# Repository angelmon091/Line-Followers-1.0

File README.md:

# Line Follower 1.0

Robot seguidor de línea — código Arduino, esquemas KiCad y Gerbers listos para fabricación.

Qué es:
- Código, PCB y archivos Gerber para un robot seguidor de línea (ejemplos en `CODE/Main Code/`).

Cómo reproducir (resumen):
1. Materiales: placa Arduino (Uno/Nano/Pro Mini), motores, driver de motores, sensores IR, batería, cables, PCB o protoboard.
2. Abrir el ejemplo: `CODE/Main Code/<ejemplo>/*.ino`.
3. Instalar librerías desde `CODE/Libreria/` y seleccionar la `board` correcta en Arduino IDE/PlatformIO.
4. Compilar y subir al microcontrolador.
5. Montar la electrónica según `ESQUEMA Y PCB/` y/o fabricar la PCB usando `Archivos Gerber PCB/gerbers/` (enviar a fabricante).

Notas importantes:
- Verificar voltaje y polaridad de la batería.
- Calibrar sensores antes de pruebas.
- Revisar conexiones del driver de motores para evitar cortocircuitos.

Estructura del proyecto (estilo `eza --tree`):
```
.
├─ CODE/
│  ├─ Libreria/
│  └─ Main Code/
│     ├─ Codigo Carro V1.0/
│     │  └─ Programacion.ino
│     ├─ Ejemplo de Lectura y Posicion/
│     │  └─ LECTURA_Y_POSICION.ino
│     └─ Ejemplo de Motores y Rotacion/
│        └─ Motores.ino
├─ ESQUEMA Y PCB/
│  ├─ asda.kicad_pcb
│  └─ asda.kicad_sch
├─ Archivos Gerber PCB/
│  └─ gerbers/
│     ├─ asda-F_Cu.gbr
│     └─ asda-job.gbrjob
├─ GErber con Turbina/
└─ README.md
```

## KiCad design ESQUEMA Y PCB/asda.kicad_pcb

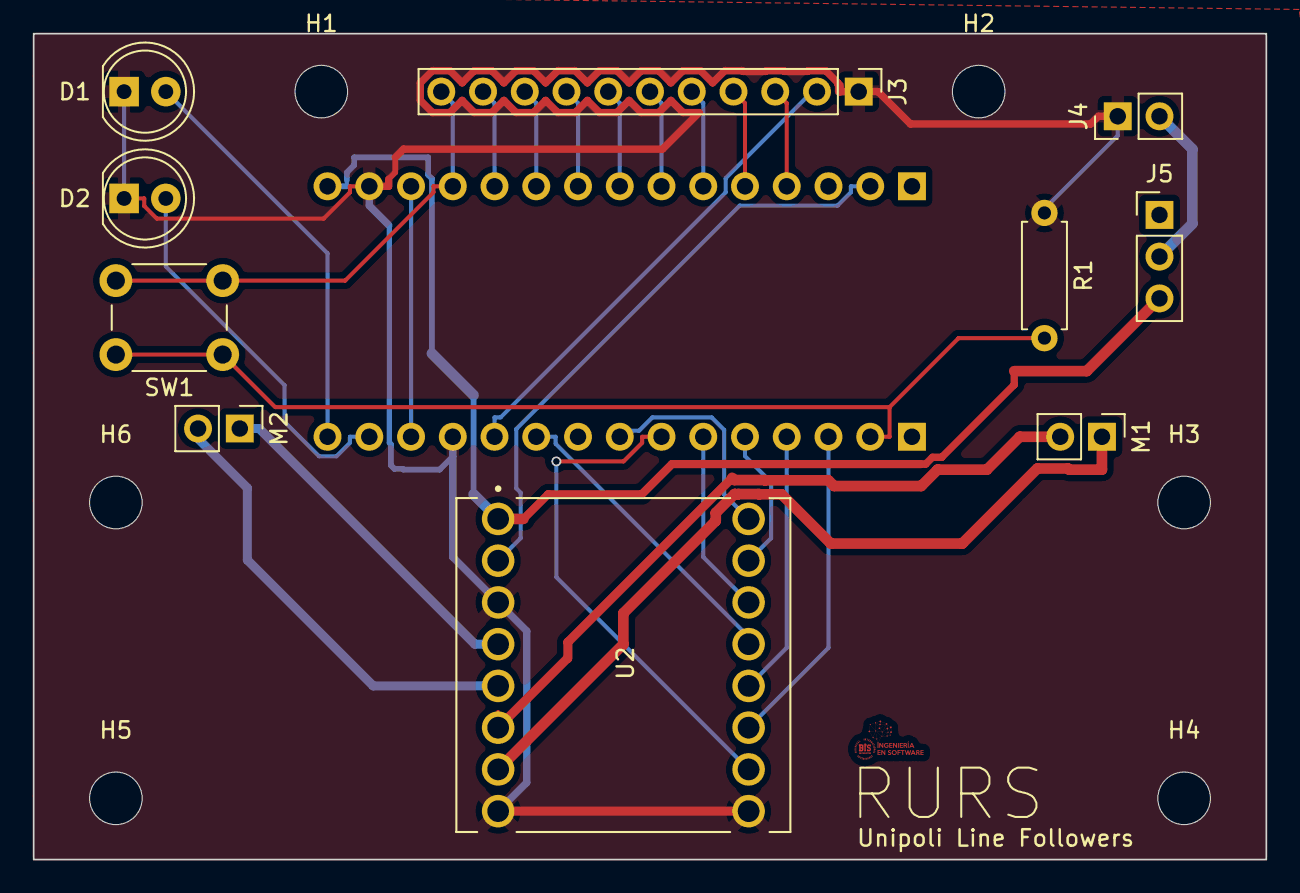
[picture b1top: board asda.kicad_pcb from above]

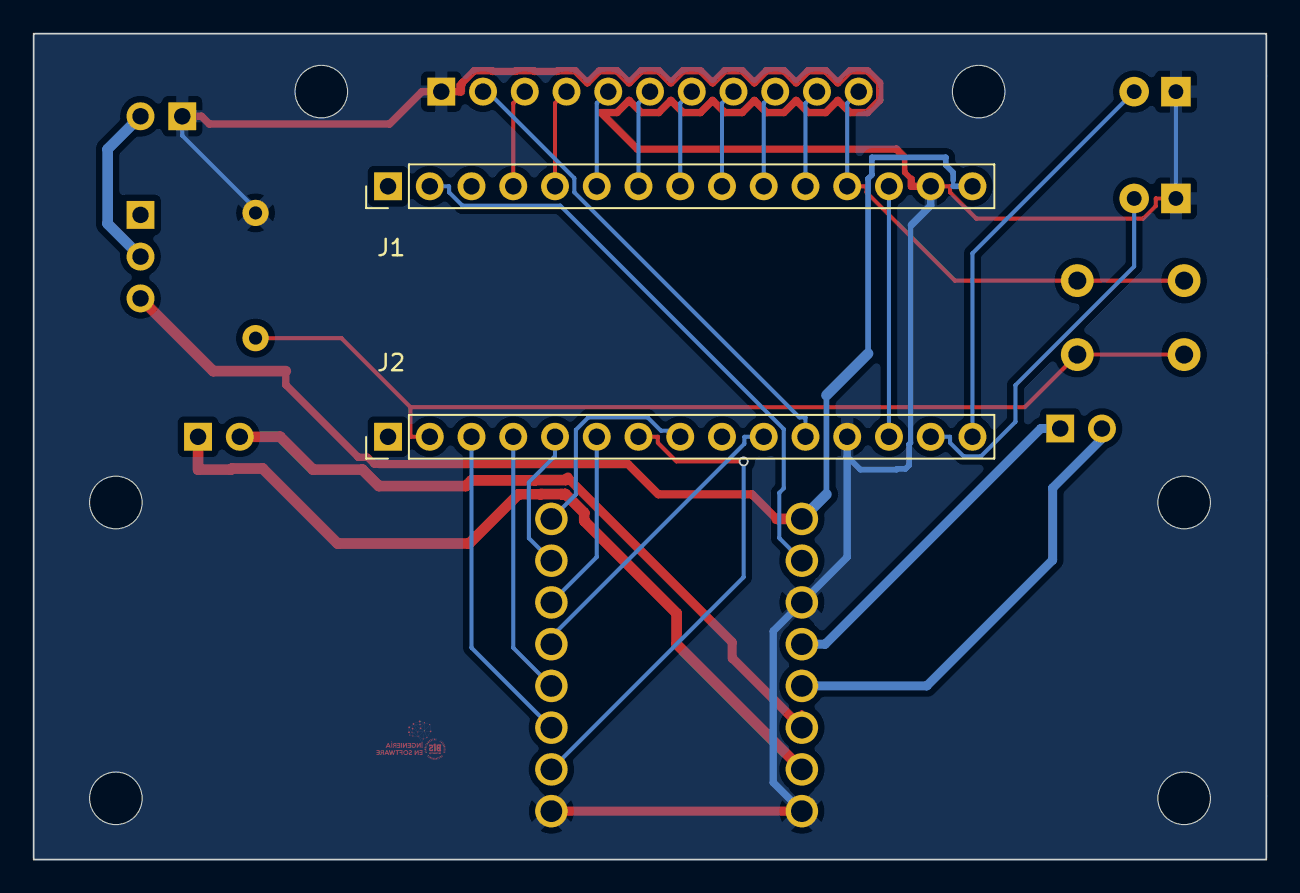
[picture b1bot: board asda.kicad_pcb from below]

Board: 2 copper layers, 75.0 x 50.2 mm, 18 parts (2 on the bottom side), 29 nets.

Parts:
D1, D2: LED; LED_D5.0mm
H1, H2, H3, H4, H5, H6: MountingHole_3.2mm_M3
J1: Analog; PinHeader_1x15_P2.54mm_Vertical
J2: Digital; PinHeader_1x15_P2.54mm_Vertical
J3: Conn_01x11; PinHeader_1x11_P2.54mm_Vertical
J4: Conn_01x02; PinHeader_1x02_P2.54mm_Vertical
J5: Conn_01x03; PinHeader_1x03_P2.54mm_Vertical
M1, M2: Motor_DC; PinHeader_1x02_P2.54mm_Vertical
R1: R; R_Axial_DIN0207_L6.3mm_D2.5mm_P7.62mm_Horizontal
SW1: SW_Push; SW_PUSH_6mm
U2: ROB-14450; MODULE_ROB-14450

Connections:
+3V3: J1.2, U2.2 (VCC)
+5V: J1.12, J3.11, SW1.2
/*D3: J2.10, U2.13 (STBY)
/*D5: J2.8, U2.16 (PWMA)
/*D6: J2.7, U2.10 (PWMB)
/*D9: J2.4, U2.12 (BI1)
/*D10/SS: J2.3, U2.11 (BI2)
/*D11/MOSI: J2.2, R1.2, SW1.1
/A0: J1.4, J3.3
/A1: J1.5, J3.4
/A2: J1.6, J3.5
/A3: J1.7, J3.6
/A4/SDA: J1.8, J3.7
/A5/SCL: J1.9, J3.8
/A6: J1.10, J3.9
/A7: J1.11, J3.10
/D0/RX: D2.2 (A), J2.14
/D1/TX: D1.2 (A), J2.15
/D2: J2.11, J3.2
/D7: J2.6, U2.14 (AI1)
/D8: J2.5, U2.15 (AI2)
/~RESET: J1.13, J2.13
GND: D1.1 (K), D2.1 (K), J1.14, J2.12, J3.1, J4.1, R1.1, U2.3 (GND), U2.8 (GND), U2.9 (GND)
unnamed: J4.2, J5.2
unnamed: M1.1 (+), U2.7 (B01)
unnamed: M1.2 (-), U2.6 (B02)
unnamed: M2.1 (+), U2.4 (A01)
unnamed: M2.2 (-), U2.5 (A02)
VCC: J1.15, J5.3, U2.1 (VM)

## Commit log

2026-06-03 Inicializacion del repozitorio
2026-06-03 Update subproject commit status to indicate dirty state in history files
2026-06-03 Update README.md with project usage instructions
2026-06-03 Update README.md to enhance project description and usage instructions
2026-06-03 Update README.md to include project structure and additional reproduction notes
